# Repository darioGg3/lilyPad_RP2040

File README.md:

# lilyPad_RP2040
 lilyPad style board with an RP2040, it was design in KiCAD 8.0 .

 Characteristics:
 - Powering via USB C or Pins (3.3V - GND).
 - Programing via USB.
 - Debugging port available SWD.
 - 128Mb Flash memory.
 - 16 GPIOs, 3 of them ADC inputs.
 - Programable LED on GPIO13.

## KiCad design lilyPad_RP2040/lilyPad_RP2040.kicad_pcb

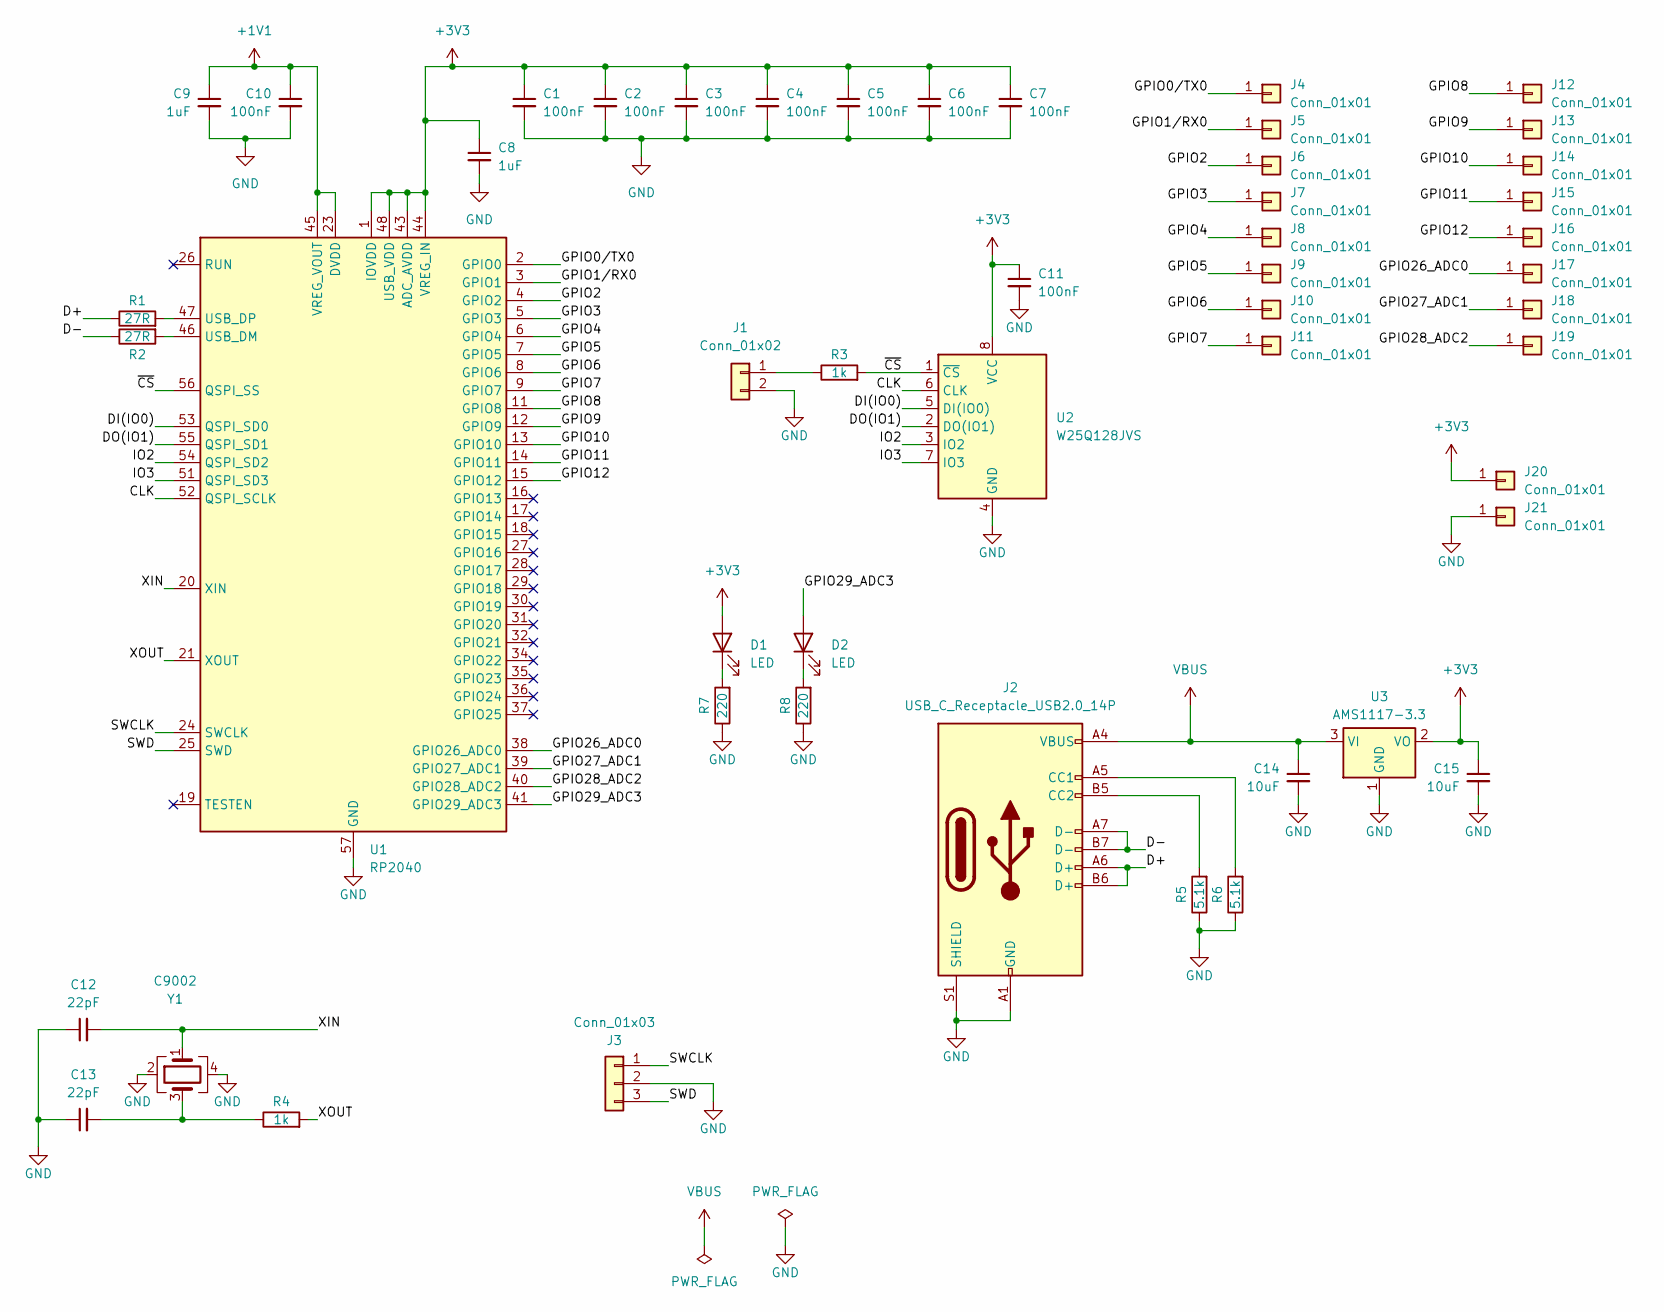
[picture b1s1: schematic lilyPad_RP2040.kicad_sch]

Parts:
C1, C2, C3, C4, C5, C6, C7, C10, C11: 100nF; C_0603_1608Metric
C8, C9: 1uF; C_0603_1608Metric
C12, C13: 22pF; C_0603_1608Metric
C14, C15: 10uF; C_0603_1608Metric
D1, D2: LED; LED_0603_1608Metric
J1: Conn_01x02; PinSocket_1x02_P2.54mm_Vertical
J2: USB_C_Receptacle_USB2.0_14P; USB_C_Receptacle_G-Switch_GT-USB-7010ASV
J3: Conn_01x03; PinSocket_1x03_P2.54mm_Vertical
J4, J5, J6, J7, J8, J9, J10, J11, J12, J13, J14, J15, J16, J17, J18, J19, J20, J21: Conn_01x01; LilyPad_Pad
R1, R2: 27R; R_0603_1608Metric
R3, R4: 1k; R_0603_1608Metric
R5, R6: 5.1k; R_0603_1608Metric
R7, R8: 220; R_0603_1608Metric
U1: RP2040; QFN-56-1EP_7x7mm_P0.4mm_EP3.2x3.2mm
U2: W25Q128JVS; SOIC-8_5.23x5.23mm_P1.27mm
U3: AMS1117-3.3; SOT-223-3_TabPin2
Y1: C9002; Crystal_SMD_3225-4Pin_3.2x2.5mm

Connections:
+1V1: C9.1, C10.1, U1.23 (DVDD), U1.45 (VREG_VOUT), U1.50 (DVDD)
+3V3: C1.1, C2.1, C3.1, C4.1, C5.1, C6.1, C7.1, C8.1, C11.1, C15.1, D1.2 (A), J20.1, U1.1 (IOVDD), U1.10 (IOVDD), U1.22 (IOVDD), U1.33 (IOVDD), U1.42 (IOVDD), U1.43 (ADC_AVDD), U1.44 (VREG_IN), U1.48 (USB_VDD), U1.49 (IOVDD), U2.8 (VCC), U3.2 (VO)
/CLK: U1.52 (QSPI_SCLK), U2.6 (CLK)
/D+: J2.A6 (D+), J2.B6 (D+), R1.1
/D-: J2.A7 (D-), J2.B7 (D-), R2.1
/DI(IO0): U1.53 (QSPI_SD0), U2.5 (DI(IO0))
/DO(IO1): U1.55 (QSPI_SD1), U2.2 (DO(IO1))
/GPIO0/TX0: J4.1, U1.2 (GPIO0)
/GPIO1/RX0: J5.1, U1.3 (GPIO1)
/GPIO2: J6.1, U1.4 (GPIO2)
/GPIO3: J7.1, U1.5 (GPIO3)
/GPIO4: J8.1, U1.6 (GPIO4)
/GPIO5: J9.1, U1.7 (GPIO5)
/GPIO6: J10.1, U1.8 (GPIO6)
/GPIO7: J11.1, U1.9 (GPIO7)
/GPIO8: J12.1, U1.11 (GPIO8)
/GPIO9: J13.1, U1.12 (GPIO9)
/GPIO10: J14.1, U1.13 (GPIO10)
/GPIO11: J15.1, U1.14 (GPIO11)
/GPIO12: J16.1, U1.15 (GPIO12)
/GPIO26_ADC0: J17.1, U1.38 (GPIO26_ADC0)
/GPIO27_ADC1: J18.1, U1.39 (GPIO27_ADC1)
/GPIO28_ADC2: J19.1, U1.40 (GPIO28_ADC2)
/GPIO29_ADC3: D2.2 (A), U1.41 (GPIO29_ADC3)
/IO2: U1.54 (QSPI_SD2), U2.3 (IO2)
/IO3: U1.51 (QSPI_SD3), U2.7 (IO3)
/SWCLK: J3.1, U1.24 (SWCLK)
/SWD: J3.3, U1.25 (SWD)
/XIN: C12.2, U1.20 (XIN), Y1.1
/XOUT: R4.2, U1.21 (XOUT)
/~CS: R3.2, U1.56 (QSPI_SS), U2.1 (~CS)
GND: C1.2, C2.2, C3.2, C4.2, C5.2, C6.2, C7.2, C8.2, C9.2, C10.2, C11.2, C12.1, C13.1, C14.2, C15.2, J1.2, J2.A1 (GND), J2.A12 (GND), J2.B1 (GND), J2.B12 (GND), J2.S1 (SHIELD), J3.2, J21.1, R5.1, R6.1, R7.1, R8.1, U1.57 (GND), U2.4 (GND), U3.1 (GND), Y1.2, Y1.4
unnamed: C13.2, R4.1, Y1.3
unnamed: D1.1 (K), R7.2
unnamed: D2.1 (K), R8.2
unnamed: J1.1, R3.1
unnamed: J2.A5 (CC1), R6.2
unnamed: J2.B5 (CC2), R5.2
unnamed: R2.2, U1.46 (USB_DM)
unnamed: R1.2, U1.47 (USB_DP)
VBUS: C14.1, J2.A4 (VBUS), J2.A9 (VBUS), J2.B4 (VBUS), J2.B9 (VBUS), U3.3 (VI)

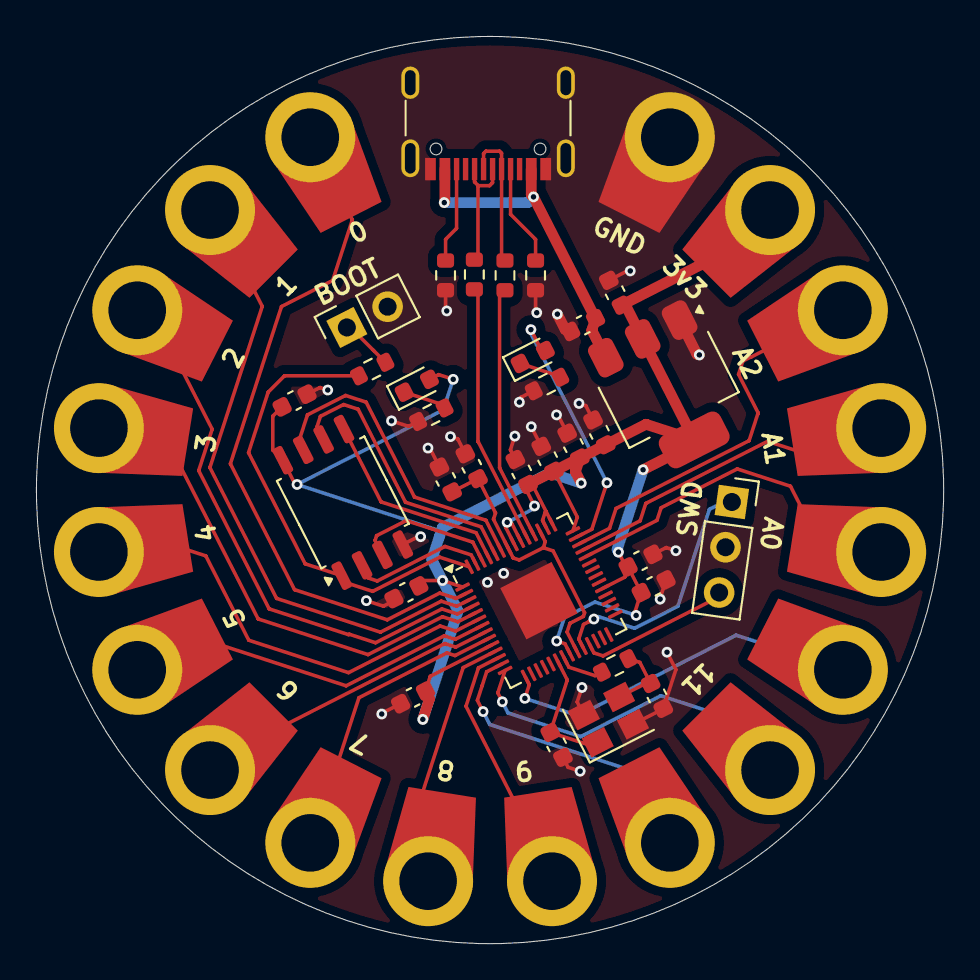
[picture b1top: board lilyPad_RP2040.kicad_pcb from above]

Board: 2 copper layers, 50.4 x 50.4 mm, 50 parts (0 on the bottom side), 41 nets.

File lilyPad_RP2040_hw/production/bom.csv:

Designator,Footprint,Quantity,Value,LCSC Part #
"C1, C10, C11, C2, C3, C4, C5, C6, C7",0603,9,100nF,
"C12, C13",0603,2,22pF,
"C14, C15",0603,2,10uF,
"C8, C9",0603,2,1uF,
"D1, D2",0603,2,LED,
J2,USB_C_Receptacle_G-Switch_GT-USB-7010ASV,1,USB_C_Receptacle_USB2.0_14P,
"R1, R2",0603,2,27R,
"R3, R4",0603,2,1k,
"R5, R6",0603,2,5.1k,
"R7, R8",0603,2,220,
U1,QFN-56-1EP_7x7mm_P0.4mm_EP3.2x3.2mm,1,RP2040,
U2,SOIC-8_5.23x5.23mm_P1.27mm,1,W25Q128JVS,
U3,SOT-223-3_TabPin2,1,AMS1117-3.3,
Y1,Crystal_SMD_3225-4Pin_3.2x2.5mm,1,C9002,

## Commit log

2024-02-27 init
2024-02-28 fonoooo
2024-03-02 finish_hw
2024-03-04 some changes
2024-03-04 added_photos
2024-03-04 resize_photos
